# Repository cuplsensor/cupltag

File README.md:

# cuplTag
The project comprises hardware and firmware. 

The firmware runs on a low power MSP430 microcontroller. It periodically reads temperature and humidity from an [HDC2022](https://www.ti.com/product/HDC2022) sensor. Readings are base-64 encoded and stored in a URL, which resides on an NFC EEPROM. 

When a phone is hovered over a cuplTag, the URL is read and a web browser opens ([demo](https://www.youtube.com/watch?v=ySxt_svazHo)). No app is required. The web application decodes, timestamps and displays readings to the user. 

## Key Features
- Average current consumption ~0.5uA. Runs for years on a CR1220 battery.
- Ease of use. No app to install on the Android / Apple phone.
- Data are automatically uploaded to the web.

[Buy one on Crowd Supply!](https://crowdsupply.com/cupl/cupltag)

## Pinout

J30 is a 2.54mm pitch 2x4 way header.

| Pin | Name | Direction | Description       | Note                           |
|-----|------|-----------|-------------------|--------------------------------|
| 1   | TX   | Output    | UART transmit     | Transmit from MSP430           |
| 2   | RX   | Input     | UART receive      | Receive to MSP430              |
| 3   | GND  |           | GND               |                                |
| 4   | TST  | Input     | Spy-Bi-Wire Clock | Also TEST signal for BSL entry |
| 5   | GND  |           | GND               |                                |
| 6   | nRST | I/O       | Spy-Bi-Wire Data  | Also active low RESET signal   |
| 7   | VDD  | Input     | Power in          | +3V3                           |
| 8   | nPRG | Input     | Prog. Mode Enable | Active low                     |

## User Documentation 

### Guides

* [Getting Started](docs/firmware/gettingstarted.rst) by loading the project into Code Composer.
* [Programming](docs/firmware/programming/index.rst) the MSP430.
* [Configuration with UART (1 of 2)](docs/guides/configUARTpt1/index.md).
* [Configuration with UART (2 of 2)](https://github.com/cuplsensor/cuplfrontend/blob/master/docs/guides/configUARTpt2/index.md) [cuplfrontend].
* [Configuration with NFC](docs/guides/configNFC/index.md).

### Interface

* [Configuration Strings](docs/specs/configstrings.rst)  that can be written over the serial port or NFC.

## Code Documentation

[ReadTheDocs](https://cupl.readthedocs.io/projects/tag/en/latest/)

## Licence

### Firmware

### Hardware

[CERN Open Hardware Licence Version 2 - Strongly Reciprocal](https://ohwr.org/cern_ohl_s_v2.txt)

### Documentation

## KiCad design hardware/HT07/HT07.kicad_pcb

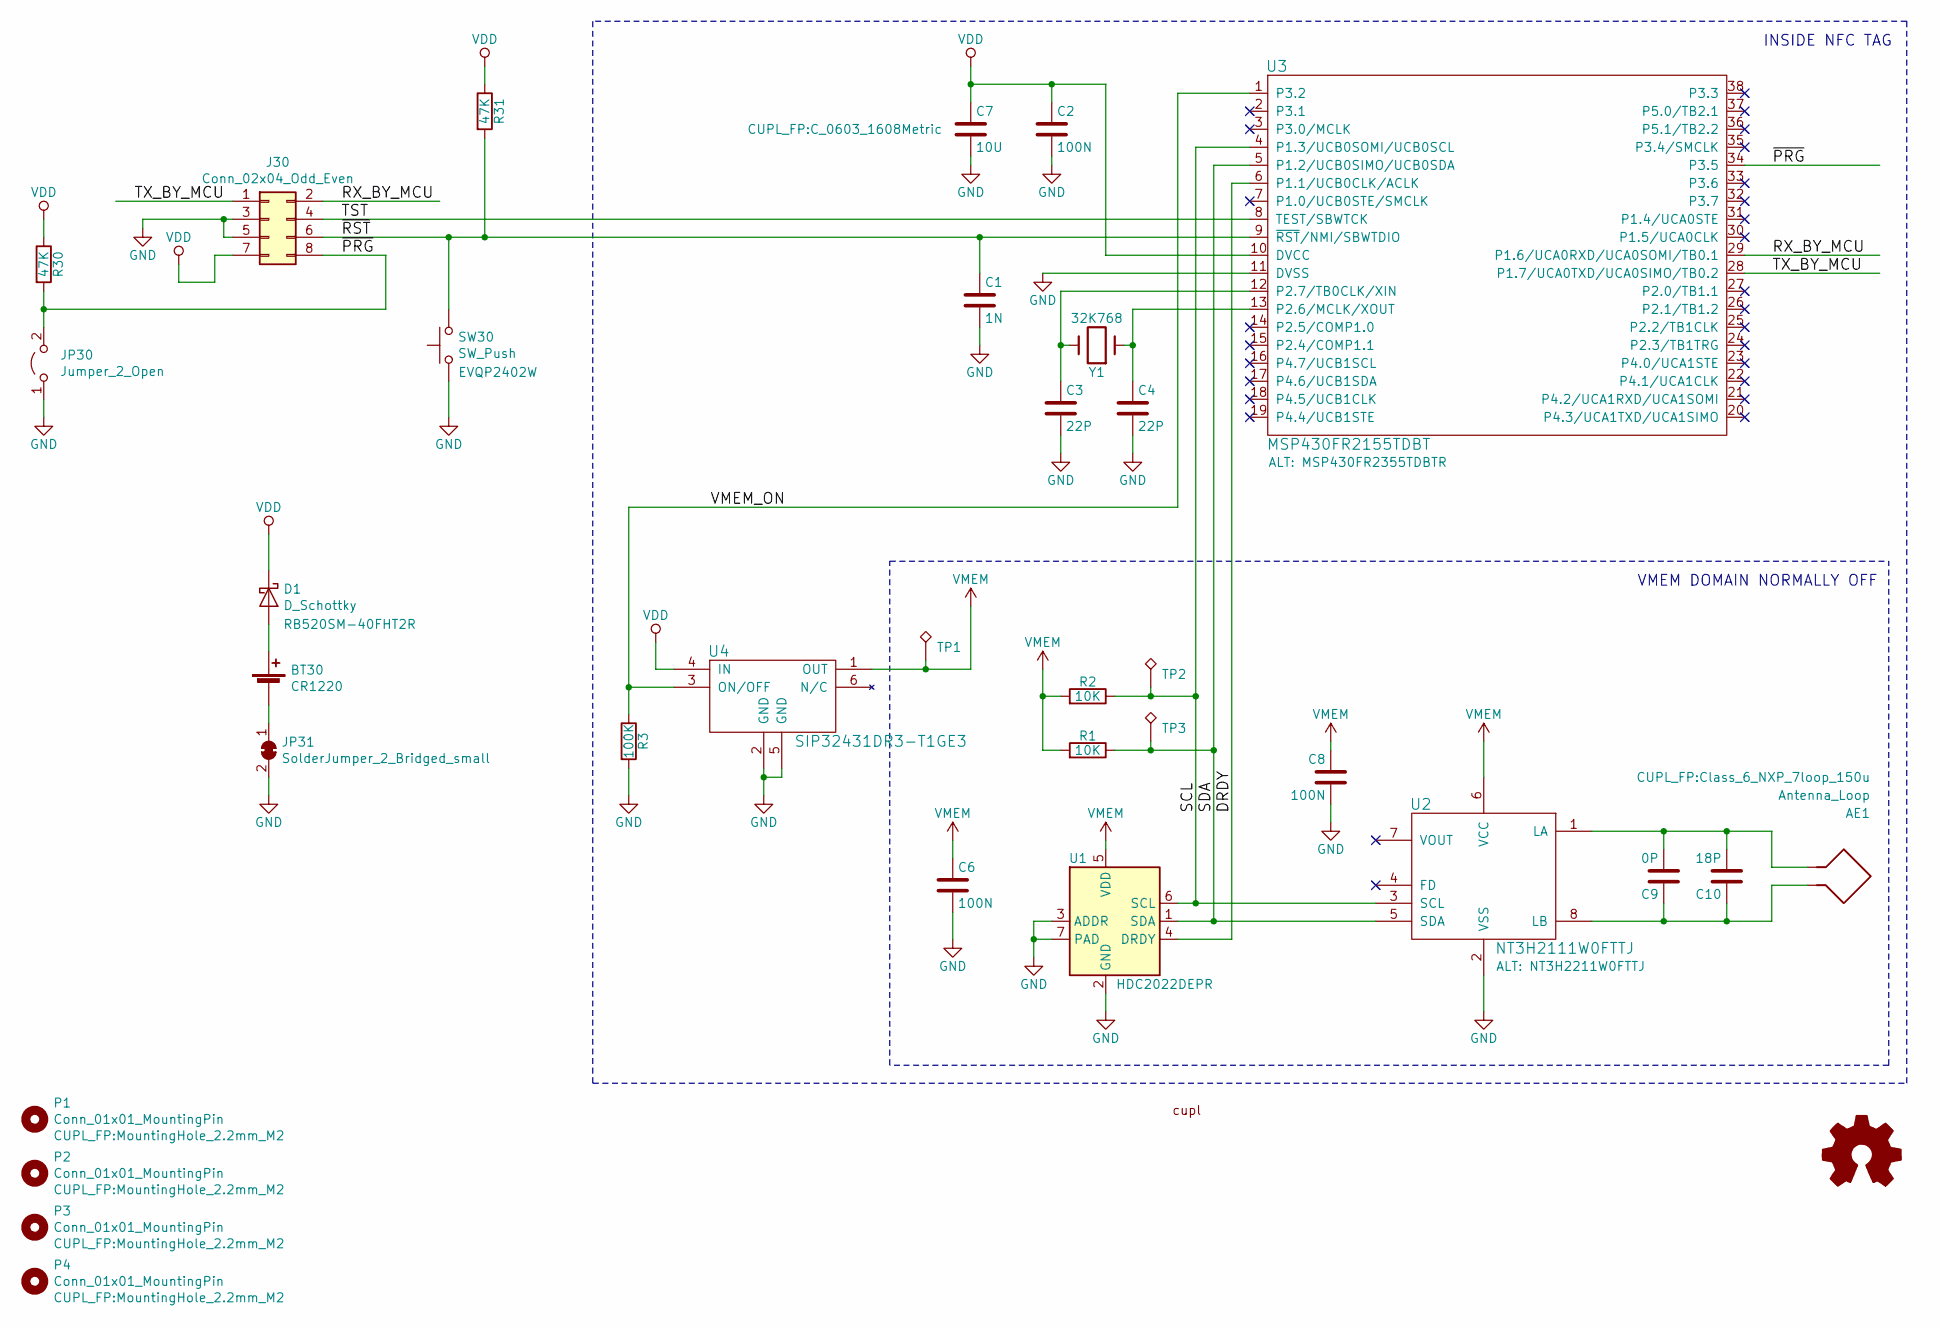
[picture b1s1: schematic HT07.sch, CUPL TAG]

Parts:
AE1: Antenna_Loop; Class_6_NXP_7loop_150u
BT30: CR1220; MPD_BC501SM_CR1220
C1: 1N; C_0402_1005Metric
C2, C6, C8: 100N; C_0402_1005Metric
C3, C4: 22P; C_0402_1005Metric
C7: 10U; C_0603_1608Metric
C9: 0P; C_0402_1005Metric
C10: 18P; C_0402_1005Metric
D1: D_Schottky; D_SOD-523
J30: Conn_02x04_Odd_Even; PinHeader_2x04_P2.54mm_Vertical
JP30: Jumper_2_Open; PinHeader_1x02_P2.54mm_Vertical
JP31: SolderJumper_2_Bridged_small; SolderJumper-2_Bridged_small
LOGO1: Logo_Open_Hardware_Small; OSHW-Logo_5.7x6mm_SilkScreen
LOGO2: CUPL; logo
P1, P2, P3, P4: Conn_01x01_MountingPin; MountingHole_2.2mm_M2
R1, R2: 10K; R_0402_1005Metric
R3: 100K; R_0402_1005Metric
R30, R31: 47K; R_0402_1005Metric
SW30: SW_Push; SW_SPST_EVQP2
TP1: MEM; TestPoint_THTPad_D1.0mm_Drill0.5mm
TP2: SCL; TestPoint_THTPad_D1.0mm_Drill0.5mm
TP3: SDA; TestPoint_THTPad_D1.0mm_Drill0.5mm
U1: HDC2022DEPR; HDC2021
U2: NT3H2111W0FTTJ; TSSOP-8_3x3mm_P0.65mm
U3: MSP430FR2155TDBT; TSSOP-38_4.4x9.7mm_P0.5mm
U4: SIP32431DR3-T1GE3; SOT-363_SC-70-6
Y1: 32K768; Crystal_SMD_2012-2Pin_2.0x1.2mm_HandSoldering

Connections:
/DRDY: U1.4 (DRDY), U3.6 (P1.1/UCB0CLK/ACLK)
/RX_BY_MCU: J30.2, U3.29 (P1.6/UCA0RXD/UCA0SOMI/TB0.1)
/SCL: R2.1, TP2.1, U1.6 (SCL), U2.3 (SCL), U3.4 (P1.3/UCB0SOMI/UCB0SCL)
/SDA: R1.1, TP3.1, U1.1 (SDA), U2.5 (SDA), U3.5 (P1.2/UCB0SIMO/UCB0SDA)
/TST: J30.4, U3.8 (TEST/SBWTCK)
/TX_BY_MCU: J30.1, U3.28 (P1.7/UCA0TXD/UCA0SIMO/TB0.2)
/VMEM_ON: R3.1, U3.1 (P3.2), U4.3 (ON/OFF)
/~PRG~: J30.8, JP30.2 (B), R30.2, U3.34 (P3.5)
/~RST~: C1.1, J30.6, R31.2, SW30.2, U3.9 (~RST~/NMI/SBWTDIO)
GND: C1.2, C2.2, C3.2, C4.2, C6.2, C7.2, C8.2, J30.3, J30.5, JP30.1 (A), JP31.2 (B), R3.2, SW30.1, U1.2 (GND), U1.3 (ADDR), U1.7 (PAD), U2.2 (VSS), U3.11 (DVSS), U4.2 (GND), U4.5 (GND)
unnamed: AE1.1, C9.2, C10.2, U2.1 (LA)
unnamed: AE1.2, C9.1, C10.1, U2.8 (LB)
unnamed: BT30.1 (+), D1.2 (A)
unnamed: BT30.2 (-), JP31.1 (A)
unnamed: C3.1, U3.12 (P2.7/TB0CLK/XIN), Y1.2
unnamed: C4.1, U3.13 (P2.6/MCLK/XOUT), Y1.1
VDD: C2.1, C7.1, D1.1 (K), J30.7, R30.1, R31.1, U3.10 (DVCC), U4.4 (IN)
VMEM: C6.1, C8.1, R1.2, R2.2, TP1.1, U1.5 (VDD), U2.6 (VCC), U4.1 (OUT)

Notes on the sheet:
VMEM DOMAIN NORMALLY OFF
INSIDE NFC TAG

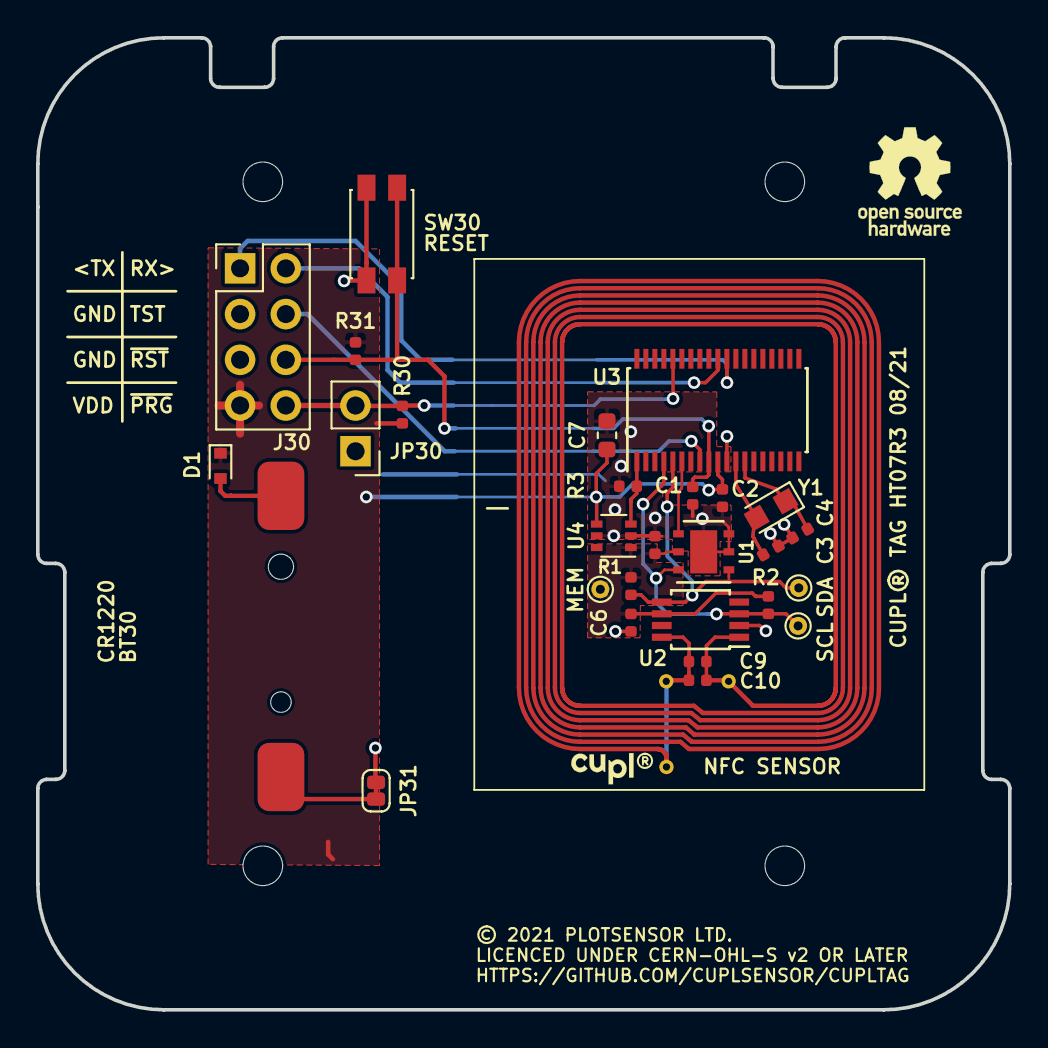
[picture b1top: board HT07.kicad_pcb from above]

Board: 2 copper layers, 54.0 x 54.0 mm, 35 parts (0 on the bottom side), 18 nets.

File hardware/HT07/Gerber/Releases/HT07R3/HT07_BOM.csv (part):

"Source:","C:\Users\malco\Documents\Plotsensor\cupltag\hardware\HT07\HT07.sch"
"Date:","29/09/2021 13:37:43"
"Tool:","Eeschema (5.1.5)-3"
"Generator:","C:\Program Files\KiCad\bin\scripting\plugins/bom_csv_grouped_by_value.py"
"Component Count:","32"

"Individual Components:"

"Item","Qty","Reference(s)","Value","LibPart","Footprint","Datasheet","ALT","COST@100","FIT","MANF","MANF#","SUPPLIER","SUPPLIER#"
"","","AE1","Antenna_Loop","device:Antenna_Loop","CUPL_FP:Class_6_NXP_7loop_150u","~","","","NF","","","",""
"","","BT30","CR1220","device:Battery_Cell","CUPL_FP:MPD_BC501SM_CR1220","~","","","","MPD","BC501SM","DIGIKEY","BC501SM-TRCT-ND"
"","","C1","1N","device:C","CUPL_FP:C_0402_1005Metric","","","","","","","",""
"","","C2","100N","device:C","CUPL_FP:C_0402_1005Metric","","","","","YAGEO","CC0402KRX7R7BB104","FARNELL","9402047"
"","","C3","22P","device:C","CUPL_FP:C_0402_1005Metric","","","","","AVX","04025A220JAT2A","FARNELL","1327634"
"","","C4","22P","device:C","CUPL_FP:C_0402_1005Metric","","","","","AVX","04025A220JAT2A","FARNELL","1327634"
"","","C6","100N","device:C","CUPL_FP:C_0402_1005Metric","","","","","YAGEO","CC0402KRX7R7BB104","FARNELL","9402047"
"","","C7","10U","device:C","CUPL_FP:C_0603_1608Metric","","","£0.115","","AVX","06036D106MAT2A","FARNELL","1833804"
"","","C8","100N","device:C","CUPL_FP:C_0402_1005Metric","","","","","YAGEO","CC0402KRX7R7BB104","FARNELL","9402047"
"","","C9","0P","device:C","CUPL_FP:C_0402_1005Metric","","","","NF","AVX","","FARNELL",""
"","","C10","18P","device:C","CUPL_FP:C_0402_1005Metric","","","","","MURATA","04025A180FAT2A","FARNELL","2332495"
"","","D1","D_Schottky","device:D_Schottky","CUPL_FP:D_SOD-523","~","","","","ROHM","RB520SM-40FHT2R","MOUSER","755-RB520SM-40FHT2R"
"","","J30","Conn_02x04_Odd_Even","Connector_Generic:Conn_02x04_Odd_Even","CUPL_FP:PinHeader_2x04_P2.54mm_Vertical","~","","","NF","","","",""
"","","JP30","Jumper_2_Open","Jumper:Jumper_2_Open","CUPL_FP:PinHeader_1x02_P2.54mm_Vertical","~","","","NF","","","",""
"","","JP31","SolderJumper_2_Bridged_small","Jumper:SolderJumper_2_Bridged","CUPL_FP:SolderJumper-2_Bridged_small","~","","","NF","","","",""
"","","LOGO1","Logo_Open_Hardware_Small","Graphic:Logo_Open_Hardware_Small","CUPL_FP:OSHW-Logo_5.7x6mm_SilkScreen","~","","","","","","",""
"","","LOGO2","CUPL","CUPL:CUPL","CUPL_FP:logo","","","","NF","","","",""
"","","P1","Conn_01x01_MountingPin","Mechanical:MountingHole","CUPL_FP:MountingHole_2.2mm_M2","~","","","NF","","","",""
"","","P2","Conn_01x01_MountingPin","Mechanical:MountingHole","CUPL_FP:MountingHole_2.2mm_M2","~","","","NF","","","",""
"","","P3","Conn_01x01_MountingPin","Mechanical:MountingHole","CUPL_FP:MountingHole_2.2mm_M2","~","","","NF","","","",""
"","","P4","Conn_01x01_MountingPin","Mechanical:MountingHole","CUPL_FP:MountingHole_2.2mm_M2","~","","","NF","","","",""
"","","R1","10K","device:R","CUPL_FP:R_0402_1005Metric","","","","","VISHAY","CRCW040210K0FKED","FARNELL","1469669"
"","","R2","10K","device:R","CUPL_FP:R_0402_1005Metric","","","","","VISHAY","CRCW040210K0FKED","FARNELL","1469669"
"","","R3","100K","device:R","CUPL_FP:R_0402_1005Metric","","","","","BOURNS","CR0402-FX-1003GLF","MOUSER","652-CR0402FX-1003GLF"
"","","R30","47K","device:R","CUPL_FP:R_0402_1005Metric","","","","","PANASONIC","ERJ2RKF4702X","FARNELL","2302806"
"","","R31","47K","device:R","CUPL_FP:R_0402_1005Metric","","","","","PANASONIC","ERJ2RKF4702X","FARNELL","2302806"
"","","SW30","SW_Push","Switch:SW_Push","CUPL_FP:SW_SPST_EVQP2","~","","","","PANASONIC","EVQP2402W","FARNELL","2860944"
"","","U1","HDC2022DEPR","CUPL:HDC2021","CUPL_FP:HDC2021","https://www.ti.com/lit/ds/symlink/hdc2021.pdf","","","","TEXAS","HDC2022DEPR","TEXAS","HDC2022DEPR"
"","","U2","NT3H2111W0FTTJ","CUPL:NT3H2111","CUPL_FP:TSSOP-8_3x3mm_P0.65mm","https://www.nxp.com/docs/en/data-sheet/NT3H2111_2211.pdf","ALT: NT3H2211W0FTTJ","","","NXP","NT3H2111W0FTTJ","FARNELL","2663150"
"","","U3","MSP430FR2155TDBT","CUPL:MSP430FR2155TDBT","CUPL_FP:TSSOP-38_4.4x9.7mm_P0.5mm","http://www.ti.com/lit/ds/symlink/msp430fr2155.pdf","ALT: MSP430FR2355TDBTR","","","TEXAS","MSP430FR2155TDBT","MOUSER","595-MSP430FR2155TDBTR"
"","","U4","SIP32431DR3-T1GE3","CUPL:SIP32431DR3-T1GE3","CUPL_FP:SOT-363_SC-70-6","http://www.farnell.com/datasheets/2049671.pdf?_ga=2.11166580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","","","","VISHAY","SIP32431DR3-T1GE3","FARNELL","2361509"
"","","Y1","32K768","CUPL:XTAL_32768HZ_3215","CUPL_FP:Crystal_SMD_2012-2Pin_2.0x1.2mm_HandSoldering","http://www.farnell.com/datasheets/1912628.pdf?_ga=2.19839915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","","£0.36530","","EPSON","FC-12M 32.7680KD-A3","DIGIKEY","SER3673CT-ND"



"Collated Components:"

"Item","Qty","Reference(s)","Value","LibPart","Footprint","Datasheet","ALT","COST@100","FIT","MANF","MANF#","SUPPLIER","SUPPLIER#"
"1","1","AE1","Antenna_Loop","device:Antenna_Loop","CUPL_FP:Class_6_NXP_7loop_150u","~","","","NF","","","",""
"2","1","BT30","CR1220","device:Battery_Cell","CUPL_FP:MPD_BC501SM_CR1220","~","","","","MPD","BC501SM","DIGIKEY","BC501SM-TRCT-ND"
"3","1","C1","1N","device:C","CUPL_FP:C_0402_1005Metric","","","","","","","",""
"4","3","C2, C6, C8","100N","device:C","CUPL_FP:C_0402_1005Metric","","","","","YAGEO","CC0402KRX7R7BB104","FARNELL","9402047"
"5","2","C3, C4","22P","device:C","CUPL_FP:C_0402_1005Metric","","","","","AVX","04025A220JAT2A","FARNELL","1327634"
"6","1","C7","10U","device:C","CUPL_FP:C_0603_1608Metric","","","£0.115","","AVX","06036D106MAT2A","FARNELL","1833804"
"7","1","C9","0P","device:C","CUPL_FP:C_0402_1005Metric","","","","NF","AVX","","FARNELL",""
"8","1","C10","18P","device:C","CUPL_FP:C_0402_1005Metric","","","","","MURATA","04025A180FAT2A","FARNELL","2332495"
"9","1","D1","D_Schottky","device:D_Schottky","CUPL_FP:D_SOD-523","~","","","","ROHM","RB520SM-40FHT2R","MOUSER","755-RB520SM-40FHT2R"
"10","1","J30","Conn_02x04_Odd_Even","Connector_Generic:Conn_02x04_Odd_Even","CUPL_FP:PinHeader_2x04_P2.54mm_Vertical","~","","","NF","","","",""
"11","1","JP30","Jumper_2_Open","Jumper:Jumper_2_Open","CUPL_FP:PinHeader_1x02_P2.54mm_Vertical","~","","","NF","","","",""
"12","1","JP31","SolderJumper_2_Bridged_small","Jumper:SolderJumper_2_Bridged","CUPL_FP:SolderJumper-2_Bridged_small","~","","","NF","","","",""
"13","1","LOGO1","Logo_Open_Hardware_Small","Graphic:Logo_Open_Hardware_Small","CUPL_FP:OSHW-Logo_5.7x6mm_SilkScreen","~","","","","","","",""
"14","1","LOGO2","CUPL","CUPL:CUPL","CUPL_FP:logo","","","","NF","","","",""
"15","4","P1, P2, P3, P4","Conn_01x01_MountingPin","Mechanical:MountingHole","CUPL_FP:MountingHole_2.2mm_M2","~","","","NF","","","",""
"16","2","R1, R2","10K","device:R","CUPL_FP:R_0402_1005Metric","","","","","VISHAY","CRCW040210K0FKED","FARNELL","1469669"
"17","1","R3","100K","device:R","CUPL_FP:R_0402_1005Metric","","","","","BOURNS","CR0402-FX-1003GLF","MOUSER","652-CR0402FX-1003GLF"
"18","2","R30, R31","47K","device:R","CUPL_FP:R_0402_1005Metric","","","","","PANASONIC","ERJ2RKF4702X","FARNELL","2302806"
"19","1","SW30","SW_Push","Switch:SW_Push","CUPL_FP:SW_SPST_EVQP2","~","","","","PANASONIC","EVQP2402W","FARNELL","2860944"
"20","1","U1","HDC2022DEPR","CUPL:HDC2021","CUPL_FP:HDC2021","https://www.ti.com/lit/ds/symlink/hdc2021.pdf","","","","TEXAS","HDC2022DEPR","TEXAS","HDC2022DEPR"
"21","1","U2","NT3H2111W0FTTJ","CUPL:NT3H2111","CUPL_FP:TSSOP-8_3x3mm_P0.65mm","https://www.nxp.com/docs/en/data-sheet/NT3H2111_2211.pdf","ALT: NT3H2211W0FTTJ","","","NXP","NT3H2111W0FTTJ","FARNELL","2663150"
"22","1","U3","MSP430FR2155TDBT","CUPL:MSP430FR2155TDBT","CUPL_FP:TSSOP-38_4.4x9.7mm_P0.5mm","http://www.ti.com/lit/ds/symlink/msp430fr2155.pdf","ALT: MSP430FR2355TDBTR","","","TEXAS","MSP430FR2155TDBT","MOUSER","595-MSP430FR2155TDBTR"
"23","1","U4","SIP32431DR3-T1GE3","CUPL:SIP32431DR3-T1GE3","CUPL_FP:SOT-363_SC-70-6","http://www.farnell.com/datasheets/2049671.pdf?_ga=2.11166580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","","","","VISHAY","SIP32431DR3-T1GE3","FARNELL","2361509"
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
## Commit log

2020-05-17 First commit.
2020-05-17 Added documentation
2020-05-17 Reorganised documentation
2020-05-17 Name change
2020-05-17 Update Doxyfile
2020-05-17 Added state chart
2020-05-17 Moved statechart
2020-05-17 statechart
2020-05-25 Added some getting started docs
2020-05-26 Documentation update
2020-05-26 Added documentation.
2020-05-26 Docs
2020-06-01 Firmware project builds.
    Old Codec references have been updated.
2020-06-21 Firmware now running on HT04
2020-06-22 Now outputs a boot message
2020-07-04 Made firmware work on new HT04 hardware.
2020-07-07 Removed field detect. Added progmode pin check to uart.
2020-07-07 Removed unused code and renamed some functions.
2020-07-07 Added some doxygen comments to main.c
2020-07-15 Fixed bug with MEM not turning on.
2020-07-20 Ensuring that UART does not cause sleep whilst nPRG is asserted.
    This keeps the tag responsive in programming mode.
2020-07-21 Improved state machines and added error messages.
    No more while(1) loops. NDEF text records added to the top of main.c
2020-07-22 Updated state chart.
2020-07-22 Documentation update.
2020-07-22 Added CC-BY-SA
2020-07-22 Added intersphinx mapping to codec
2020-07-22 Added hardware documentation.
2020-07-22 Increase image width.
2020-07-22 Cropped pinout.
2020-07-22 Moved HT04_pinout.svg
2020-07-22 Pinout table.
2020-07-22 Expanded documentation.
2020-07-22 Documented configuration
2020-08-08 Altered version string and added voltage check.
2020-12-02 Even parity added.
2020-12-08 Updated firmware.
2020-12-16 Added i2c_off and updated docs for HT05
2021-01-19 Added nt3h.c and batv.c from cuplcodec 2.0.9
    Also added a scan for an NT3H when its I2C device has been inadvertently changed. Added <x: > around the version string.
2021-01-30 Flattened codebase. Licence text.
2021-01-30 Removed HTS221.c. No longer used.
2021-02-07 Reduced current consumption by using LPM3.5
    Sleep current measured as 420nA in LPM3.5, which is down from 1.5uA in LPM3 used previously. Many variables have been moved to FRAM, using the PERSISTENT pragma and the intiailisation of these have h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
2021-04-06 Updated firmware to work with HT07
2021-04-19 Removed nt3h_init
2021-04-19 Frequency of external oscillator measured as 32.7685 kHz
2021-04-19 Moved HT07rev2 from the private repo.
    Also removed debug features from main.c (for testing 32.768 kHz XTAL frequency).
2021-04-21 HT07R2 sent to manufacture at Eurocircuits
2021-04-24 Added turbo mode
    In turbo mode, temperature and humidity are sampled at 1Hz. Also added a 3 second delay at startup, before measuring the battery voltage. Finally nt3h_check_address has been modified to return 1 when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
2021-04-28 Fixed a bug in nt3h_update_cc
    In the event of an error, rxData can be read back as zero so it is important to set rxData[0] to the device each time, otherwise the device address can also change to zero.
2021-04-30 SVS does not cause a stall unless battery level is low.
2021-05-04 Issued evaluation board for new HT07R2.
2021-08-16 Clear the NT3H lock to I2C
    Also increased update time from 1s to 3s in turbo mode.
2021-08-29 Up-issued to Rev 3
    This changes the humidity sensor to HDC2022 from HDC2021. Also adds alternate parts for the MSP430 and NT3H to the schematic.
2021-09-27 Started to update documentation.
2021-09-27 Corrected bullet points
2021-09-27 Programming mode screenshot added.
2021-09-27 Minor formatting mod
2021-09-27 Fixing styles.
2021-09-27 Revert "Update conf.py"
    This reverts commit 98aedcead40b62f004159848f9dfc79b8142e12d.
2021-09-27 Formatting
2021-09-28 Moved configuration strings into a new doc
2021-09-28 Added configuration part 1 of 2.
2021-09-29 Added configuration with UART part 2.
2021-09-29 Added gerbers
2022-01-04 Fixed excess current draw >0.5uA in LPM3.5 bug.
    Current varied based on temperature and hand placement etc. Much higher than the 0.5uA expected in LPM3.5. Pull up/down resistors were not explicitly defined for all pins. P3.5 (nPRG) was set as an i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
2022-02-03 Documentation updated
2022-02-17 More comments added.
2022-03-29 Added system block diagram for the front page
2022-03-29 Changed to PNG after problems with SVG
2022-03-29 Made arrows clearer
2022-06-21 Added some docstrings.
2022-07-05 Documented stat.c
2022-07-05 Reducing nesting.
2022-07-05 Correcting errors in document structure.
2022-07-05 Minor docs bugfix.
2022-07-16 Added docstring to init_errorcheck
2022-07-17 More docstrings added to main.c
2022-07-17 Added some file docstrings
2022-07-17 Minor tweak to docstrings
2022-07-17 Added more state charts
2022-07-17 Fixing the toc
2022-07-17 Not using variable substitution in UML
    It looks like this is not supported.
2022-07-17 Added descriptions to the state charts
2022-07-17 Removed unused states from the state charts
2022-07-17 Removed width 100%
2022-08-04 Docstrings update.
2022-08-05 Refactored NT3H module and added docstrings.
2022-08-23 Added doxygen comments to I2C driver
2022-08-23 Added table recognition to sphinx.
2022-08-25 Added docstrings for confignfc
2022-08-26 Refeactored NVParams.c
2022-08-26 grammar correction
2022-08-26 Added battery voltage docs
2022-12-26 Bump wheel from 0.33.6 to 0.38.1 in /docs
    Bumps [wheel](https://github.com/pypa/wheel) from 0.33.6 to 0.38.1.
    - [Release notes](https://github.com/pypa/wheel/releases)
    - [Changelog](https://github.com/pypa/wheel/blob/main/docs/news.rst)
    - [Commits](https://github.com/pypa/wheel/compare/0.33.6...0.38.1)
    ---
    updated-dependencies:

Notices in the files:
README.md:
License: GPL v3
License: CC BY-SA 4.0
hardware/HT07/HT07.kicad_pcb:
© 2021 PLOTSENSOR LTD.
LICENCED UNDER CERN-OHL-S v2 OR LATER
hardware/HT07/HT07.sch:
COPYRIGHT Plotsensor Ltd. 2021
Licenced under CERN OHL-v2-S
